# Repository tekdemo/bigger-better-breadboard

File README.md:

A Bigger Better Breadboard
===========================
A ridiculously large 10x scale breadboard, with complete breadboard functionality and some basic components.

But, why?
---------
Because it's neat! This was designed by [OSH Park](https://oshpark.com) for the PDX Mini Maker Faire 2014, as a way to help demonstrate
some simple basic breadboard skills and circuits. 

Among the common issues we've incounted during workshops, demos, and clases:
- It's not immediately apparent how a breadboard works, and can be tough to explain and double check
- Breadboards are really tiny, so it's hard to use for demonstration.
- Exposed wire leads will short out together, and can be a frusturating experience for newcomers.
- Small kids want to learn, but tend to wreck component leads, making it hard for them and others to work with. 
- Small kids and small parts can be bad. 
- Inexperienced users will eventually do something wrong and burn out your parts. But, failure creates learning opportunities that they won't get by avoiding them. We want to encourage those failures. 
- Small parts can be tough to just fiddle with, and lead to some overwhelming demos.

So, we tried to make something a bit more robust, visible, beginner friendly, and fun! This is the result.

Details
-------
The README files in individual subfolders for the components have technical details for that section of the project. 

License
--------
This design is intended to be open hardware, and is licensed under [Creative Commons Attribution, Share-Alike 3.0](http://creativecommons.org/licenses/by-sa/3.0/)
If this license prohibits you from enjoying this project, please let us know so we can consider adjusting the license.

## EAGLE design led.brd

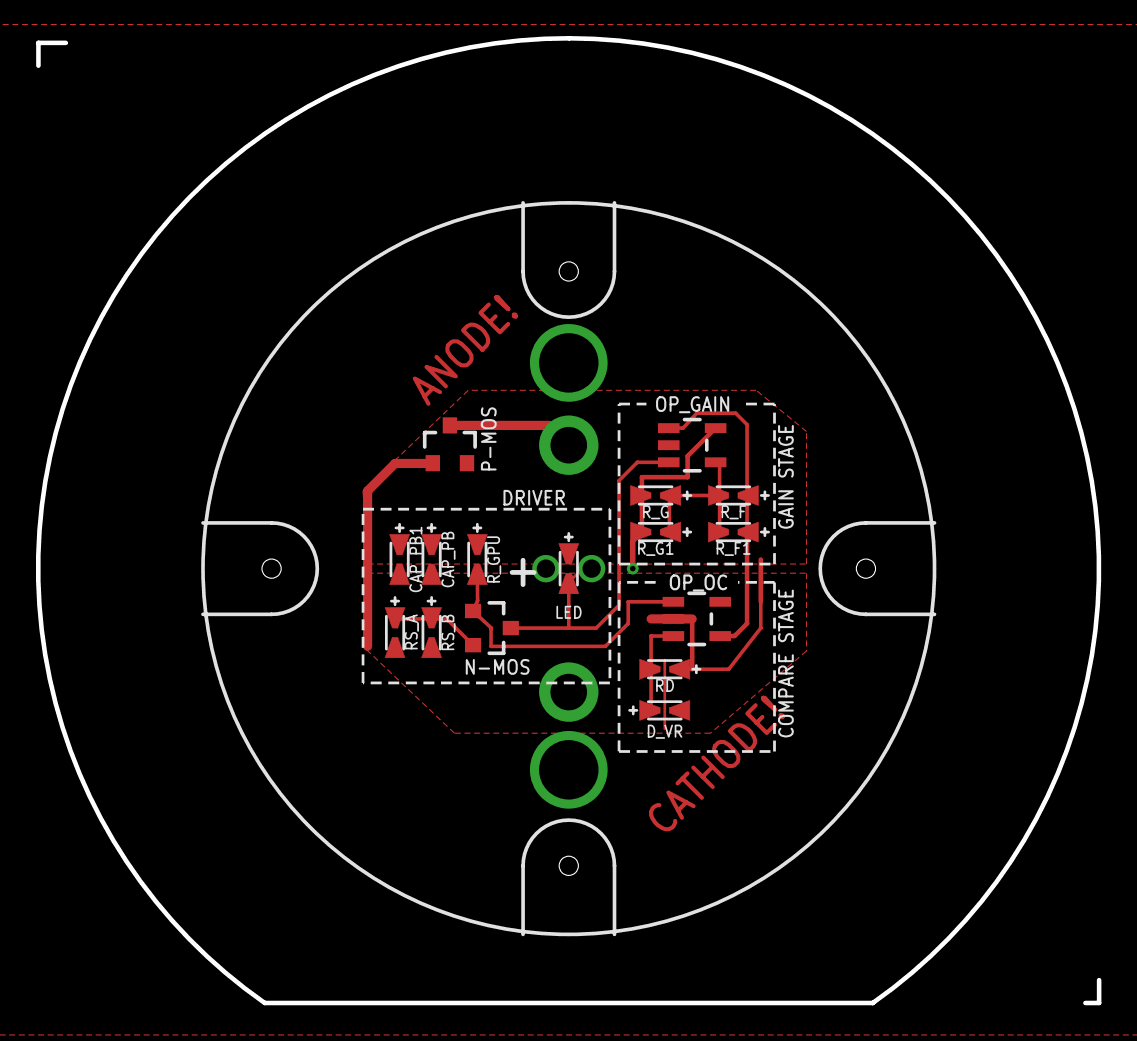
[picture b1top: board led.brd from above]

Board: 2 copper layers, 58.9 x 53.6 mm, 16 parts (0 on the bottom side), 8 nets.

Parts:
CAP_PB, CAP_PB1: 0.1uf; 0402-0603-0805-UNIVERSAL
D_VR: 0402-0603-0805-UNIVERSAL
LED: 0402-0603-0805-UNIVERSAL
N-MOS: MOSFET-NCHANNELSMD; SOT23-3
OP_GAIN: SOT23-5
OP_OC: OPA344; SOT23-5
P-MOS: SOT23-3
RD: 10k; 0402-0603-0805-UNIVERSAL
RS_A: 1ohm; 0402-0603-0805-UNIVERSAL
RS_B: NONE; 0402-0603-0805-UNIVERSAL
R_F: 9-10k; 0402-0603-0805-UNIVERSAL
R_F1: 0402-0603-0805-UNIVERSAL
R_G: 1kohm; 0402-0603-0805-UNIVERSAL
R_G1: 0402-0603-0805-UNIVERSAL
R_GPU: 10k; 0402-0603-0805-UNIVERSAL

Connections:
GATE: N-MOS.1, OP_OC.1, R_GPU.-
GND: CAP_PB.-, CAP_PB1.-, D_VR.-, OP_GAIN.5, OP_OC.5, P-MOS.1, RS_A.-, RS_B.-, R_G.-, R_G1.-
unnamed: N-MOS.2, RS_A.+, RS_B.+
VCC: CAP_PB.+, CAP_PB1.+, LED.+, OP_GAIN.2, OP_OC.2, P-MOS.2, RD.+, R_GPU.+
VDIV: OP_GAIN.4, R_F.-, R_F1.-, R_G.+, R_G1.+
VREF: D_VR.+, OP_OC.3, RD.-
VSENSE: LED.-, N-MOS.3, OP_GAIN.3
V_AMP: OP_GAIN.1, OP_OC.4, R_F.+, R_F1.+

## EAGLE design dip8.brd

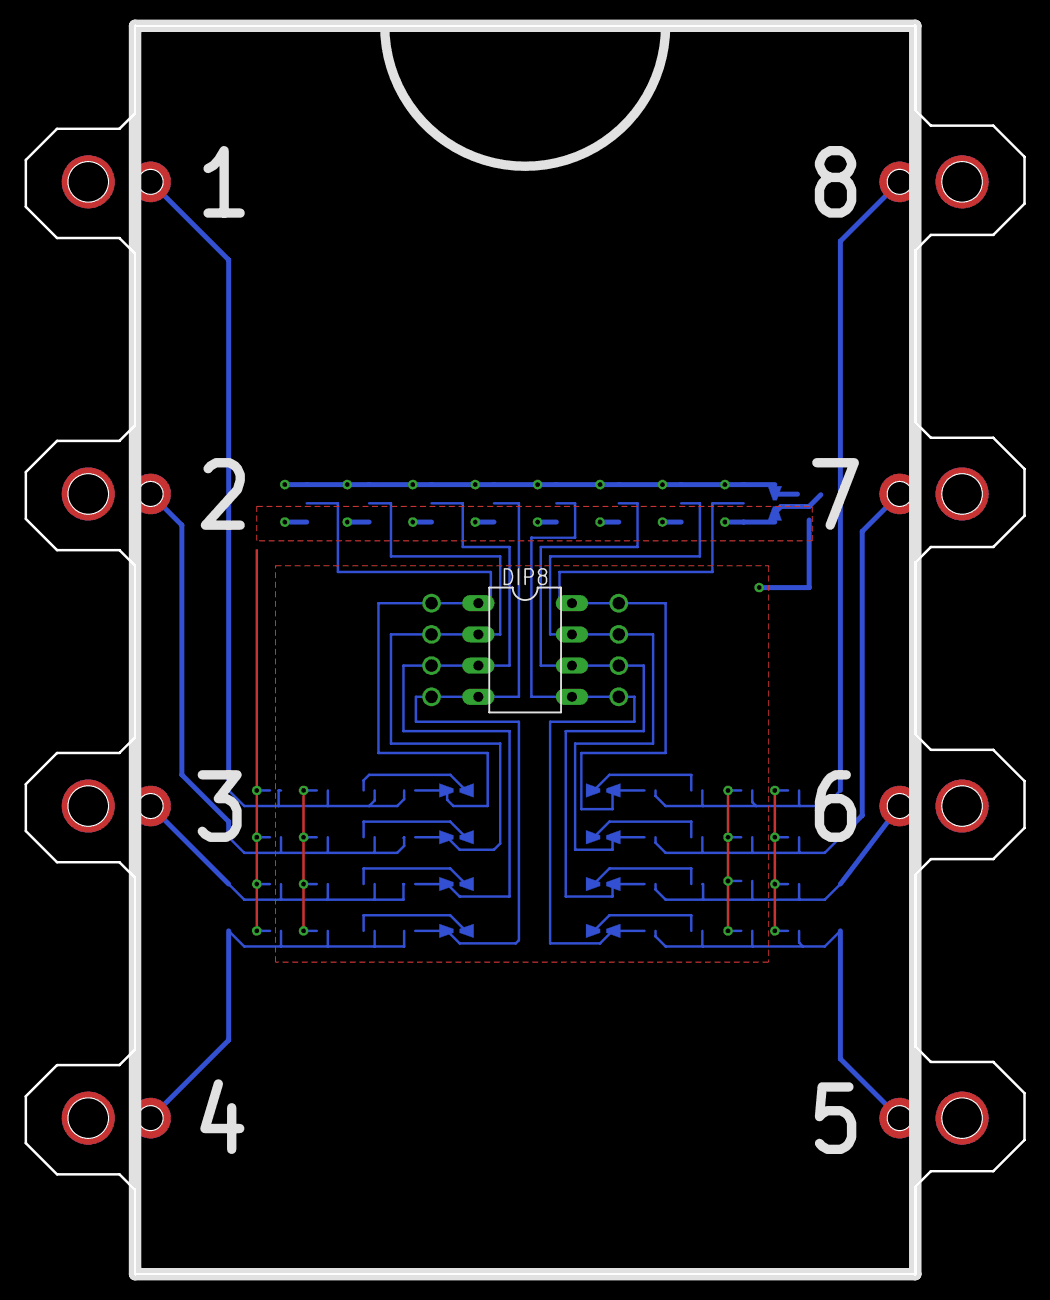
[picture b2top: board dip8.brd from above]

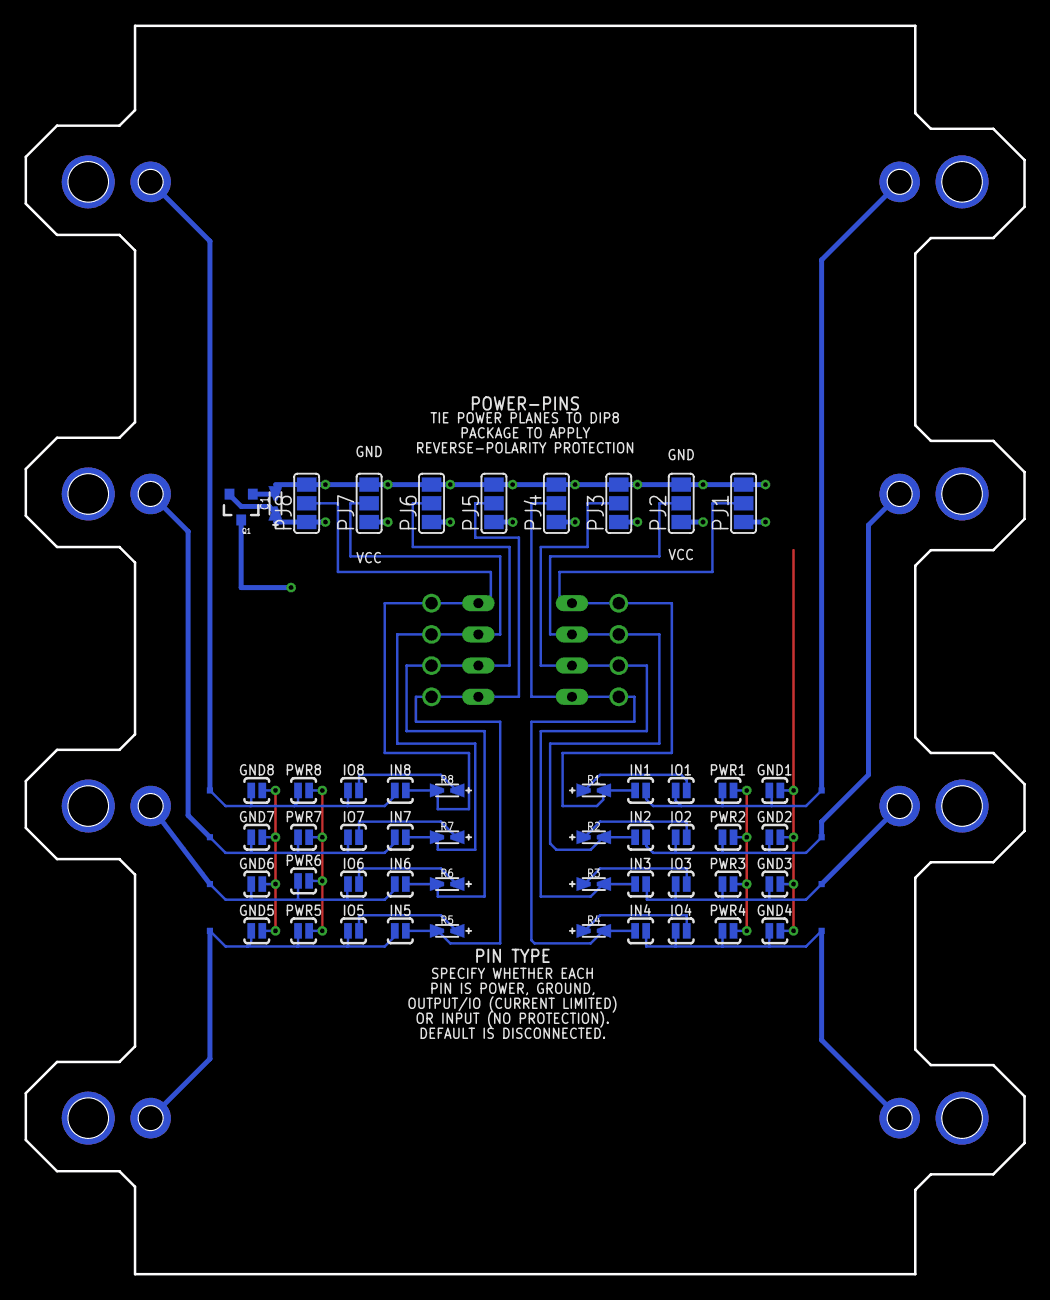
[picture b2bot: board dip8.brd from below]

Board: 2 copper layers, 81.3 x 101.6 mm, 59 parts (58 on the bottom side), 27 nets.

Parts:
C1: 0402-0603-0805-UNIVERSAL
DIP8: DIL08
GND1, GND2, GND3, GND4, GND5, GND6, GND7, GND8: SJ_2S-NO
IN1, IN2, IN3, IN4, IN5, IN6, IN7, IN8: SJ_2S-NO
IO1, IO2, IO3, IO4, IO5, IO6, IO7, IO8: SJ_2S-NO
PJ1, PJ2, PJ3, PJ4, PJ5, PJ6, PJ7, PJ8: SJ_2
PWR1, PWR2, PWR3, PWR4, PWR5, PWR6, PWR7, PWR8: SJ_2S-NO
Q1: MOSFET-PCHANNEL; SOT23-3
R1, R2, R3, R4, R5, R6, R7, R8: 0402-0603-0805-UNIVERSAL
TP1, TP2, TP3, TP4, TP5, TP6, TP7, TP8: TEST-POINT2; PAD.02X.02

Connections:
C1: GND1.1, IN1.2, IO1.1, PWR1.1, TP1.P$1
C2: GND2.1, IN2.2, IO2.1, PWR2.1, TP2.P$1
C3: GND3.1, IN3.2, IO3.1, PWR3.1, TP3.P$1
C4: GND4.1, IN4.2, IO4.1, PWR4.1, TP4.P$1
C5: GND5.1, IN5.1, IO5.1, PWR5.1, TP5.P$1
C6: GND6.1, IN6.1, IO6.1, PWR6.1, TP6.P$1
C7: GND7.1, IN7.1, IO7.1, PWR7.1, TP7.P$1
C8: GND8.1, IN8.1, IO8.1, PWR8.1, TP8.P$1
GND: C1.-, GND1.2, GND2.2, GND3.2, GND4.2, GND5.2, GND6.2, GND7.2, GND8.2, PJ1.3, PJ2.3, PJ3.3, PJ4.3, PJ5.3, PJ6.3, PJ7.3, PJ8.3, Q1.1
unnamed: IO1.2, R1.+
unnamed: IO2.2, R2.+
unnamed: IO3.2, R3.+
unnamed: IO4.2, R4.+
unnamed: IO5.2, R5.+
unnamed: IO6.2, R6.+
unnamed: IO7.2, R7.+
unnamed: IO8.2, R8.+
P1: DIP8.1, IN1.1, PJ1.2, R1.-
P2: DIP8.2, IN2.1, PJ2.2, R2.-
P3: DIP8.3, IN3.1, PJ3.2, R3.-
P4: DIP8.4, IN4.1, PJ4.2, R4.-
P5: DIP8.5, IN5.2, PJ5.2, R5.-
P6: DIP8.6, IN6.2, PJ6.2, R6.-
P7: DIP8.7, IN7.2, PJ7.2, R7.-
P8: DIP8.8, IN8.2, PJ8.2, R8.-
VCC: C1.+, PJ1.1, PJ2.1, PJ3.1, PJ4.1, PJ5.1, PJ6.1, PJ7.1, PJ8.1, Q1.2
VIN: PWR1.2, PWR2.2, PWR3.2, PWR4.2, PWR5.2, PWR6.2, PWR7.2, PWR8.2, Q1.3

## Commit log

2014-07-26 init
2014-07-26 prototype 3 as cut
2014-07-26 Rotated power rail holes to make assembly easier.
2014-07-27 Adding stencil for painting the boards
2014-07-27 Added a large stencil for single-pass painting
2014-07-27 Updated paths for stencil
2014-07-27 Generated stencils for each paint color
2014-08-05 added 3d models!
2014-08-05 a few tweaks to things
2014-09-01 updated 3D models to have cm for units
2014-09-01 prototype for 10x parts in pcb shapes
2014-09-01 correct LED circuit
2014-09-01 routed led board
2014-09-02 embiggened resitor
2014-09-08 confirm footprints and finalize for maker faire
2014-09-15 Added finishing touches to DIP8
2014-09-15 Removed short caused by old bad footprint
2014-12-15 Massive Documentation cleanup
    - Reorganized file structure
    - Add Readme files
    - Create BOM placeholders
    - Fill out readme files
    - Add picture of project
2014-12-15 Minor correrctions to documentation
2014-12-15 Can't spell
2014-12-16 Add BOM to breadboard
2014-12-16 Add capacitor part list
2014-12-16 Update part BOMs, correct minor varistor issue
2014-12-16 Adjusted table alignment

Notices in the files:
parts and their libraries:
SparkFun-Passives: Licensing: Creative Commons ShareAlike 4.0 International - https://creativecommons.org/licenses/by-sa/4.0
